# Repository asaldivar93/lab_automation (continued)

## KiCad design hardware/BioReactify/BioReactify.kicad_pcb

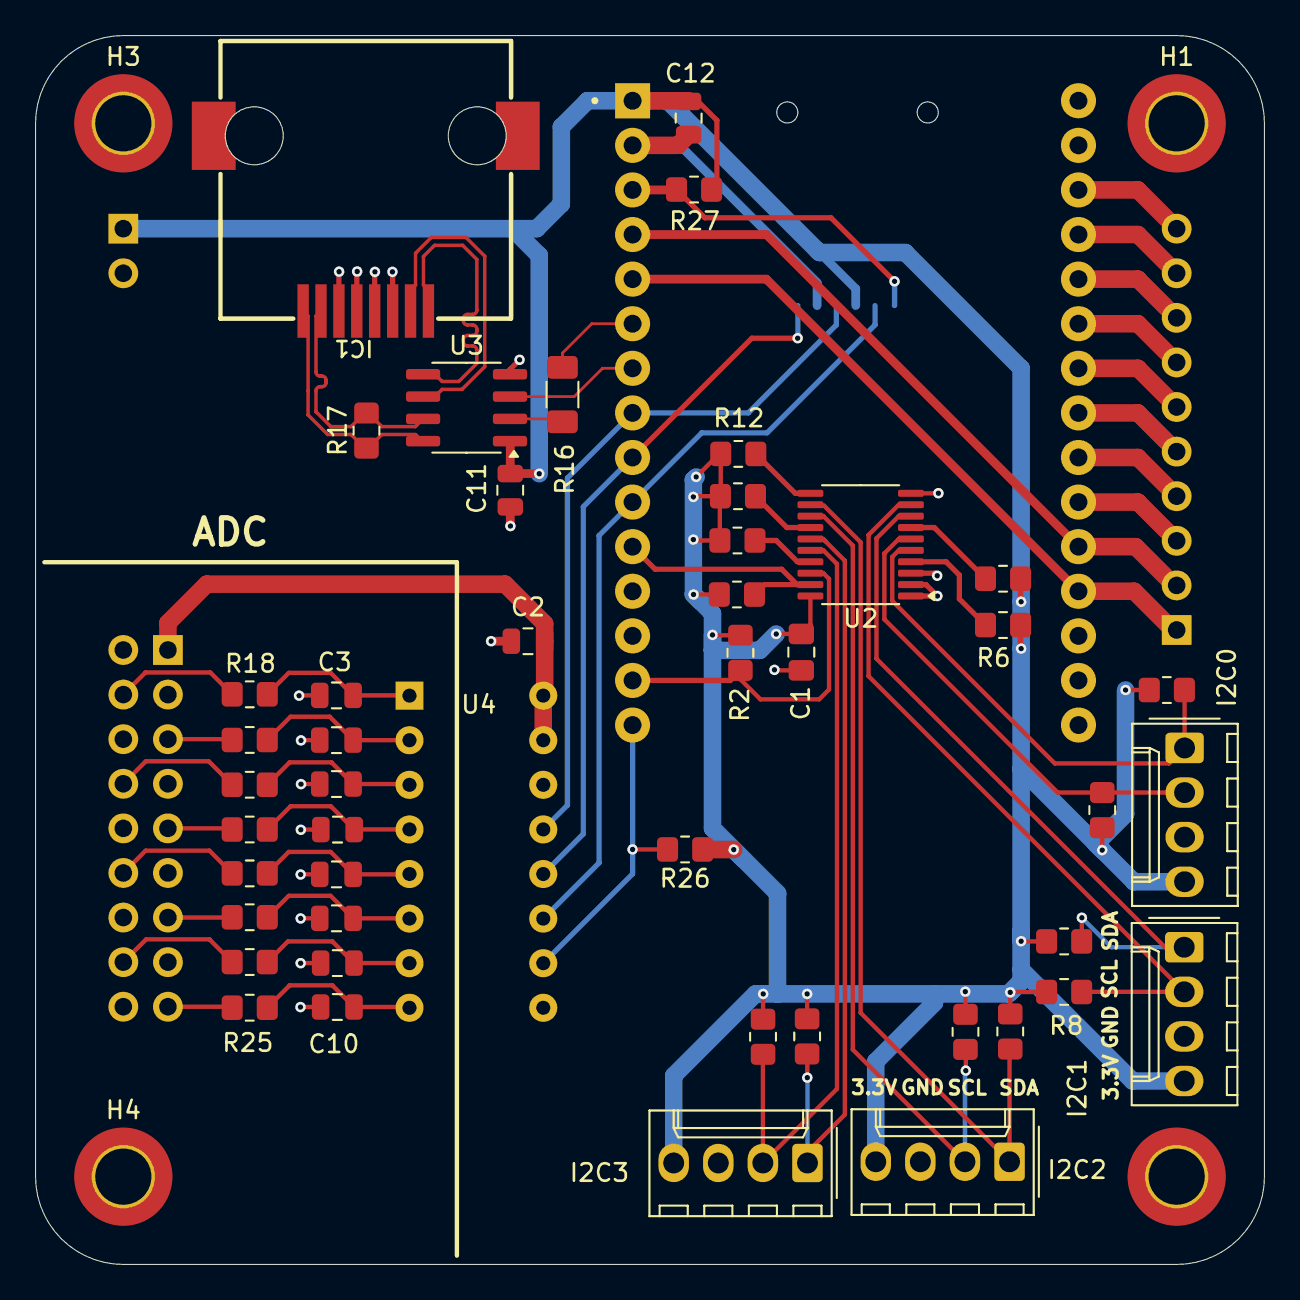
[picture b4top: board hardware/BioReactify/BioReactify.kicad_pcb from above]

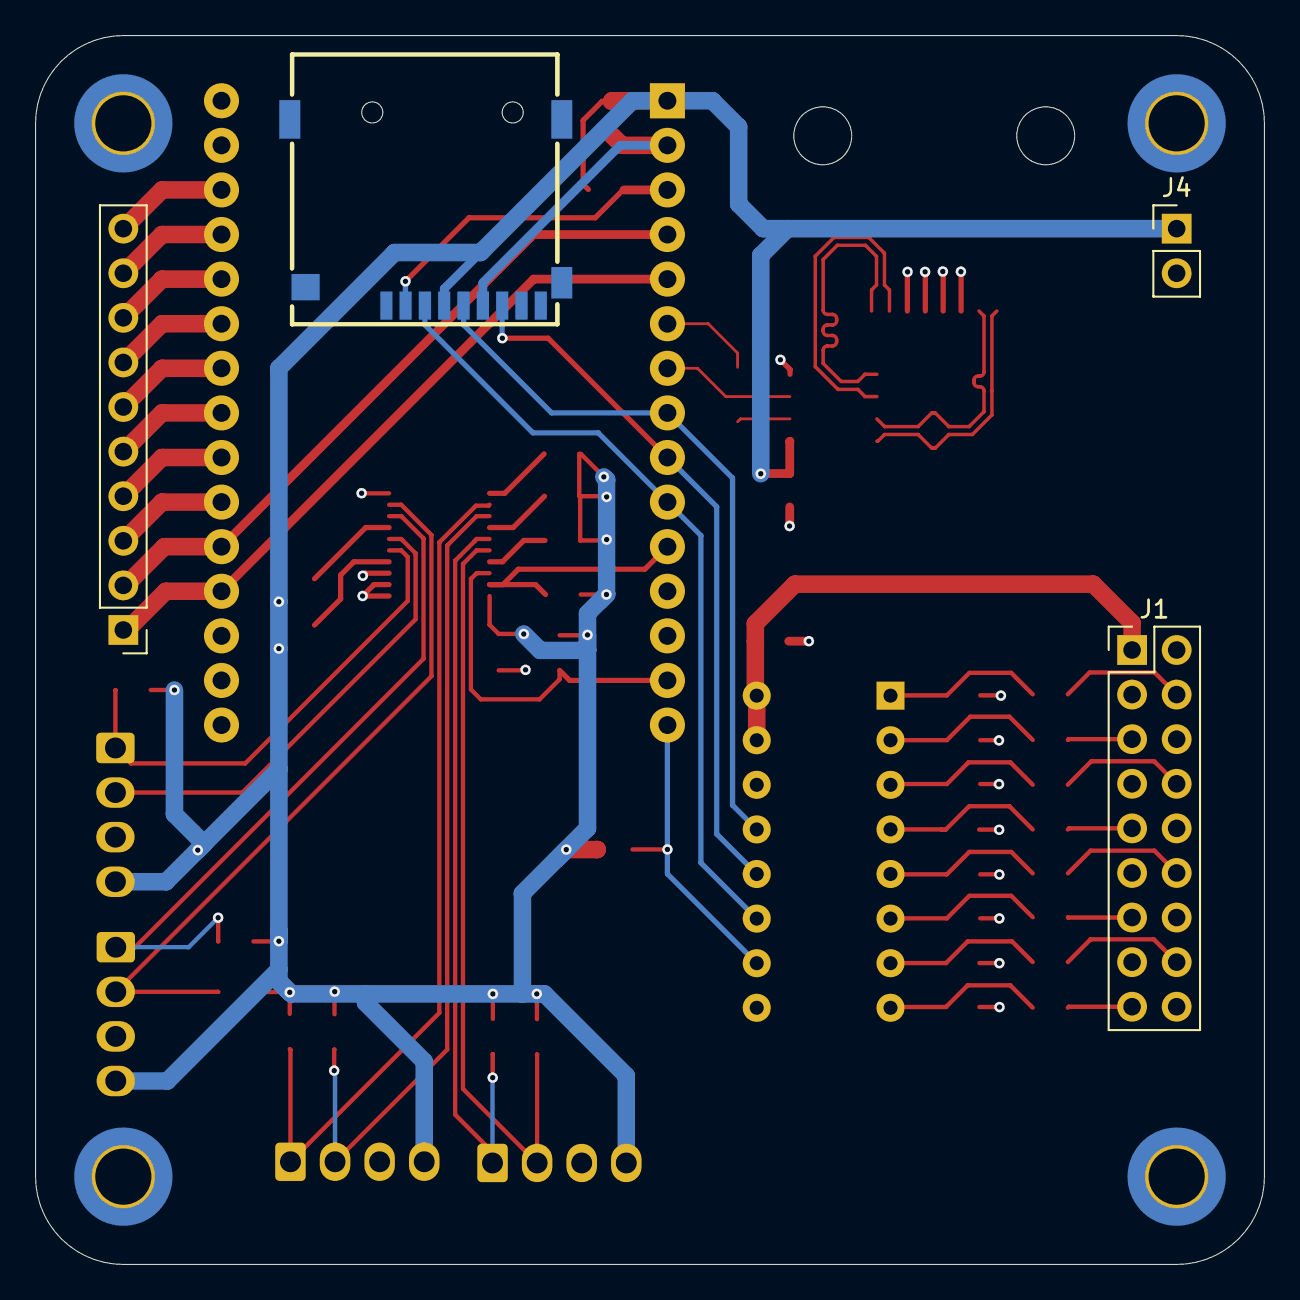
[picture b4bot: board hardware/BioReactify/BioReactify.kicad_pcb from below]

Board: 4 copper layers, 70.0 x 70.0 mm, 56 parts (4 on the bottom side), 56 nets.

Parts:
C1: 10uF; C_0805_2012Metric_Pad1.18x1.45mm_HandSolder
C2, C11, C12: 10uF; C_0805_2012Metric
C3, C4, C5, C6, C7, C8, C9, C10: 0.022uF; C_0805_2012Metric
H1, H2, H3, H4: MountingHole_Pad; MountingHole_3.2mm_M3_DIN965_Pad_TopBottom
I2C0, I2C1, I2C2, I2C3: Conn_01x04_Pin; Molex_KK-254_AE-6410-04A_1x04_P2.54mm_Vertical
IC1: MJ5688-B111-HR1-C; RJ45-TH_MJ5688-B111-HR1-C
J1: Conn_02x09_Odd_Even; PinHeader_2x09_P2.54mm_Vertical
J2: Conn_01x10_Pin; PinHeader_1x10_P2.54mm_Vertical
J3: Micro_SD_Card; TF-SMD_THD2528-11SD-GF
J4: Conn_01x02_Pin; PinHeader_1x02_P2.54mm_Vertical
R1, R2, R3, R4, R5, R6, R7, R8, R9, R10, R11, R12, R13, R14, R15, R26, R27: 10K; R_0805_2012Metric_Pad1.20x1.40mm_HandSolder
R16: 0; R_1206_3216Metric_Pad1.30x1.75mm_HandSolder
R17, R18, R19, R20, R21, R22, R23, R24, R25: 100; R_0805_2012Metric_Pad1.20x1.40mm_HandSolder
U1: ESP32-DEVKIT-V1; MODULE_ESP32_DEVKIT_V1
U2: TCA9544A; TSSOP-20_4.4x6.5mm_P0.65mm
U3: MAX3490xSA; SOIC-8_3.9x4.9mm_P1.27mm
U4: MCP3208; DIP-16_W7.62mm_Socket

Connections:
+3.3VADC: C2.1, J1.1, U4.15 (Vref), U4.16 (Vdd)
/ADC/CH0: C3.1, R18.1, U4.1 (CH0)
/ADC/CH1: C4.1, R19.1, U4.2 (CH1)
/ADC/CH2: C5.1, R20.1, U4.3 (CH2)
/ADC/CH3: C6.1, R21.1, U4.4 (CH3)
/ADC/CH4: C7.1, R22.1, U4.5 (CH4)
/ADC/CH5: C8.1, R23.1, U4.6 (CH5)
/ADC/CH6: C9.1, R24.1, U4.7 (CH6)
/ADC/CH7: C10.1, R25.1, U4.8 (CH7)
/ADC/INCH0: J1.4, R18.2
/ADC/INCH1: J1.5, R19.2
/ADC/INCH2: J1.8, R20.2
/ADC/INCH3: J1.9, R21.2
/ADC/INCH4: J1.12, R22.2
/ADC/INCH5: J1.13, R23.2
/ADC/INCH6: J1.16, R24.2
/ADC/INCH7: J1.17, R25.2
/CS: R26.2, U1.15 (D23), U4.10 (~CS/SHDN)
/CS1: J3.2 (DAT3/CD), R27.2, U1.3 (D15)
/D2: J2.2, U1.4 (D2), U1.20 (D35)
/D4: J2.1, U1.5 (D4), U1.19 (D34)
/DAC1: J2.5, U1.23 (D25)
/DAC2: J2.6, U1.24 (D26)
/I2C/INT0: R6.2, U2.4 (~INT0)
/I2C/INT1: R9.2, U2.7 (~INT1)
/I2C/INT2: R12.2, U2.11 (~INT2)
/I2C/INT3: R15.2, U2.14 (~INT3)
/I2C/SC0: I2C0.2, R5.2, U2.6 (SC0)
/I2C/SC1: I2C1.2, R8.2, U2.9 (SC1)
/I2C/SC2: I2C2.2, R11.2, U2.13 (SC2)
/I2C/SC3: I2C3.2, R14.2, U2.16 (SC3)
/I2C/SD0: I2C0.1, R4.2, U2.5 (SD0)
/I2C/SD1: I2C1.1, R7.2, U2.8 (SD1)
/I2C/SD2: I2C2.1, R10.2, U2.12 (SD2)
/I2C/SD3: I2C3.1, R13.2, U2.15 (SD3)
/MISO: J3.7 (DAT0), U1.9 (D18), U4.12 (Dout)
/MOSI: J3.3 (CMD), U1.10 (D19), U4.11 (Din)
/RS485/R0: R16.2, U3.2 (RO)
/RS485/RX2: R16.1, U1.6 (RX2)
/RS485/RX_N: IC1.2, R17.2, U3.7 (B)
/RS485/RX_P: IC1.1, R17.1, U3.8 (A)
/RS485/TX2: U1.7 (TX2), U3.3 (DI)
/RS485/TX_N: IC1.7, U3.6 (Z)
/RS485/TX_P: IC1.8, U3.5 (Y)
/SCL: R2.2, U1.14 (D22), U2.18 (SCL)
/SCLK: J3.5 (CLK), U1.8 (D5), U4.13 (CLK)
/SDA: R1.2, U1.11 (D21), U2.19 (SDA)
GND: C1.2, C2.2, C3.2, C4.2, C5.2, C6.2, C7.2, C8.2, C9.2, C10.2, C11.2, C12.2, H1.1, H2.1, H3.1, H4.1, I2C0.3, I2C1.3, I2C2.3, I2C3.3, IC1.3, IC1.4, IC1.5, IC1.6, J1.2, J1.3, J1.6, J1.7, J1.10, J1.11, J1.14, J1.15, J1.18, J3.6 (VSS), J4.2, U1.2 (GND), U1.29 (GND), U2.1 (A0), U2.2 (A1), U2.3 (A2), U2.10 (GND), U3.4 (GND), U4.9 (DGND), U4.14 (AGND)
unnamed: J2.3, U1.21 (D32)
unnamed: J2.4, U1.22 (D33)
unnamed: J2.7, U1.25 (D27)
unnamed: J2.8, U1.26 (D14)
unnamed: J2.9, U1.27 (D12)
unnamed: J2.10, U1.28 (D13)
unnamed: R3.2, U2.17 (~INT)
VDD: C1.1, C11.1, C12.1, I2C0.4, I2C1.4, I2C2.4, I2C3.4, J3.4 (VDD), J4.1, R1.1, R2.1, R3.1, R4.1, R5.1, R6.1, R7.1, R8.1, R9.1, R10.1, R11.1, R12.1, R13.1, R14.1, R15.1, R26.1, R27.1, U1.1 (3V3), U2.20 (VCC), U3.1 (VCC)

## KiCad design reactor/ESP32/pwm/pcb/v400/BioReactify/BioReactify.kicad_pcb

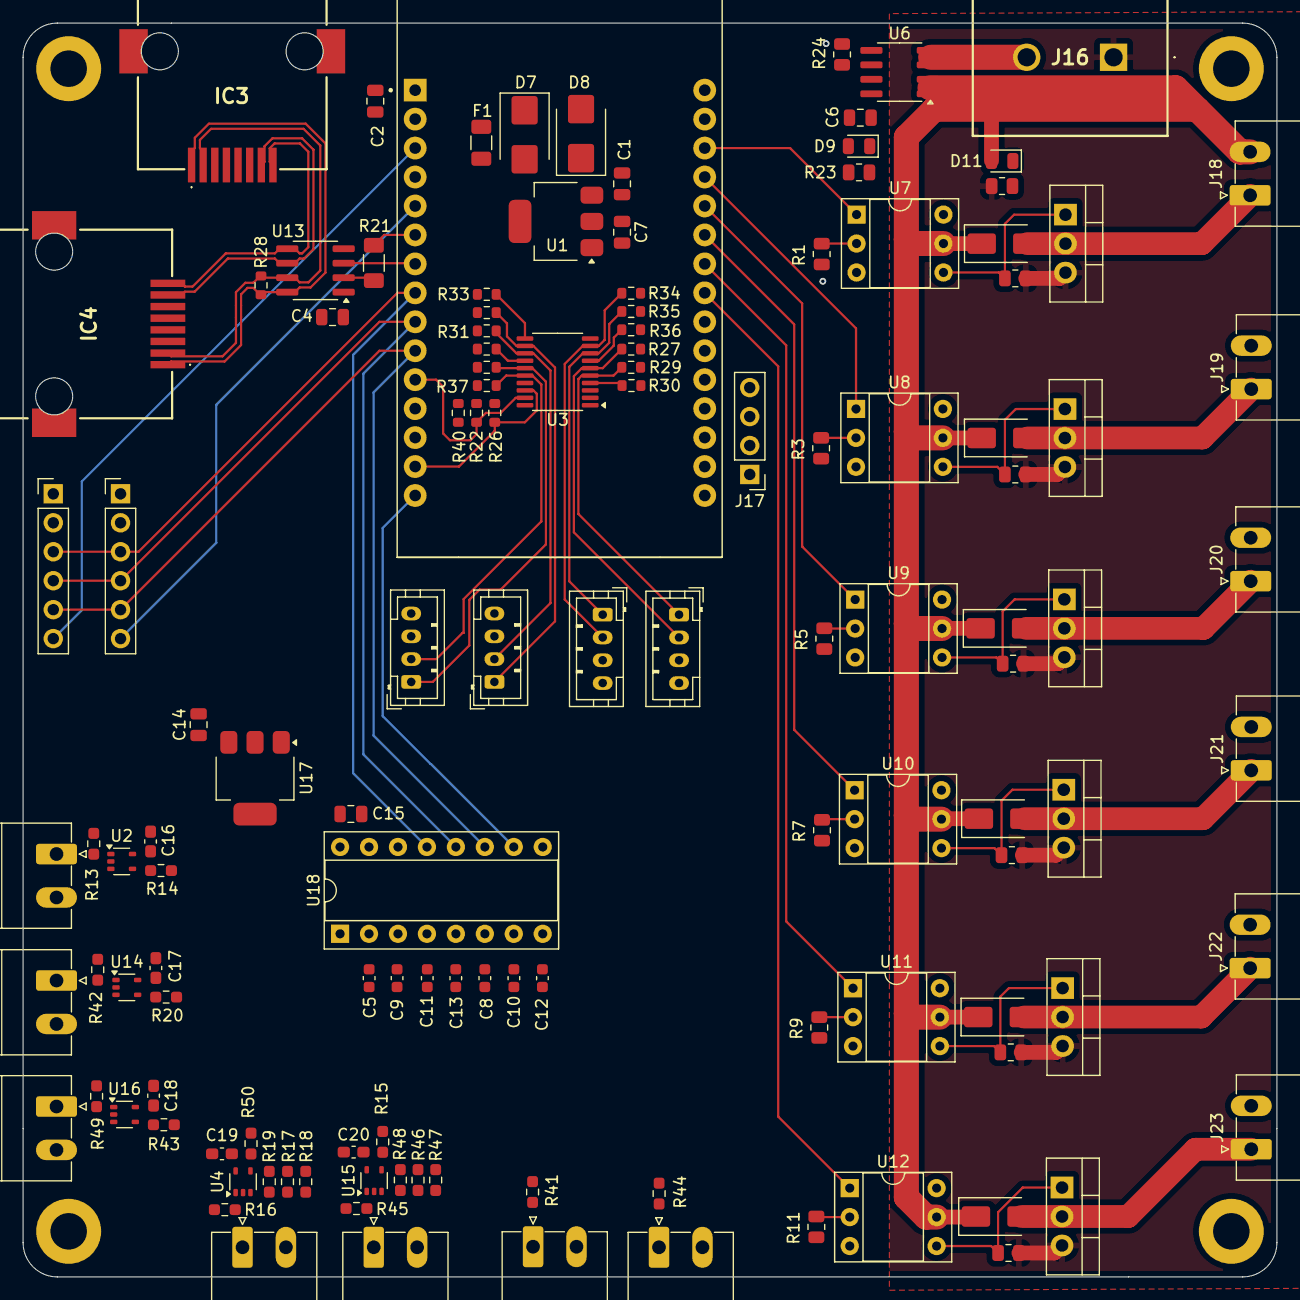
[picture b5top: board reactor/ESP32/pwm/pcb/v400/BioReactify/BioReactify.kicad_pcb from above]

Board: 4 copper layers, 110.0 x 110.0 mm, 131 parts (0 on the bottom side), 89 nets.

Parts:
C1, C14: 100nF; C_0805_2012Metric
C2, C4, C6, C7, C15: 10uF; C_0805_2012Metric
C5, C8, C9, C10, C11, C12, C13: 0.047uf; C_0603_1608Metric
C16, C17, C18, C19, C20: 0.1uF; C_0603_1608Metric_Pad1.08x0.95mm_HandSolder
D1, D2, D3, D4, D5, D6: 50V 5A; D_SMA
D7: 50V 2A; D_SMB
D8: 5.1V; D_SMB
D9, D11: LED; LED_0805_2012Metric
F1: 6V 1.5A; Fuse_1206_3216Metric
H1, H2, H3, H4: MountingHole_Pad; MountingHole_3.2mm_M3_ISO7380_Pad
IC3, IC4: MJ5688-B111-HR1-C; MJ5688B111HR1C
J1, J2, J3, J4, J5, J6, J7, J18, J19, J20, J21, J22, J23: Conn_01x02; PhoenixContact_MC_1,5_2-G-3.81_1x02_P3.81mm_Horizontal
J9, J10: Conn_01x06_Pin; PinHeader_1x06_P2.54mm_Vertical
J11, J12, J13, J14: Conn_01x04_Pin; JST_PH_B4B-PH-K_1x04_P2.00mm_Vertical
J16: KF25C-7.62-2P; KF25C7622P
J17: Conn_01x04_Pin; PinHeader_1x04_P2.54mm_Vertical
Q1, Q2, Q3, Q4, Q5, Q6: IRLZ44N; TO-220-3_Vertical
R1, R3, R5, R7, R9, R11, R23: 100; R_0805_2012Metric
R2, R4, R6, R8, R10, R12: 470; R_0805_2012Metric
R13, R42, R49: 150; R_0603_1608Metric_Pad0.98x0.95mm_HandSolder
R14, R15, R20, R41, R43, R44, R50: 3.4K; R_0603_1608Metric_Pad0.98x0.95mm_HandSolder
R16, R45: 7.8K; R_0603_1608Metric_Pad0.98x0.95mm_HandSolder
R17, R18, R46, R47: 4.1K; R_0603_1608Metric_Pad0.98x0.95mm_HandSolder
R19, R48: 1.5K; R_0603_1608Metric_Pad0.98x0.95mm_HandSolder
R21: 0; R_1206_3216Metric_Pad1.30x1.75mm_HandSolder
R22, R26, R27, R29, R30, R31, R32, R33, R34, R35, R36, R37, R38, R39, R40: 10K; R_0603_1608Metric
R24: 10K; R_0805_2012Metric
R25: 550; R_0805_2012Metric
R28: 120; R_0603_1608Metric
U1, U17: LD1117S33TR_SOT223; SOT-223-3_TabPin2
U2, U4, U14, U15, U16: TLV9001IDCK; SOT-353_SC-70-5
U3: TCA9544A; TSSOP-20_4.4x6.5mm_P0.65mm
U5: ESP32-DEVKIT-V1; MODULE_ESP32_DEVKIT_V1
U6: ACS712xLCBTR-030B3; SOIC-8_3.9x4.9mm_P1.27mm
U7, U8, U9, U10, U11, U12: 4N25; DIP-6_W7.62mm_Socket
U13: MAX3490xSA; SOIC-8_3.9x4.9mm_P1.27mm
U18: MCP3208; DIP-16_W7.62mm_Socket

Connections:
+3.3V: C2.1, C4.1, C6.1, C7.1, D9.2 (A), J9.1, J10.1, J11.4, J12.4, J13.4, J14.4, R22.1, R24.1, R26.1, R27.1, R29.1, R30.1, R31.1, R32.1, R33.1, R34.1, R35.1, R36.1, R37.1, R38.1, R39.1, R40.1, U1.2 (VO), U3.20 (VCC), U5.1 (3V3), U6.8 (VCC), U13.1 (VCC)
+3.3VADC: C15.1, C16.1, C17.1, C18.1, C19.1, C20.1, J4.1, J5.1, R17.2, R46.2, U2.5 (V+), U4.5 (V+), U14.5 (V+), U15.5 (V+), U16.5 (V+), U17.2 (VO), U18.15 (Vref), U18.16 (Vdd)
+12V: D1.1 (K), D2.1 (K), D3.1 (K), D4.1 (K), D5.1 (K), D6.1 (K), D11.2 (A), J18.2, J19.2, J20.2, J21.2, J22.2, J23.2, U6.1 (IP+), U6.2 (IP+), U7.5, U8.5, U9.5, U10.5, U11.5, U12.5
-12V: J16.1, Q1.3 (S), Q2.3 (S), Q3.3 (S), Q4.3 (S), Q5.3 (S), Q6.3 (S), R2.2, R4.2, R6.2, R8.2, R10.2, R12.2, R25.1
/5v_protected: C1.1, C14.1, D7.1 (K), D8.1 (K), U1.3 (VI), U17.3 (VI)
/12v_in: J16.2, U6.3 (IP-), U6.4 (IP-)
/CH0: U6.7 (VIOUT), U18.1 (CH0)
/CS0: U5.15 (D23), U18.10 (~CS/SHDN)
/CS2: J9.6, U5.5 (D4)
/CS3: J10.6, U5.3 (D15)
/D32: J17.3, U5.21 (D32)
/D33: J17.4, U5.22 (D33)
/D34: J17.2, U5.20 (D35)
/D35: J17.1, U5.19 (D34)
/FETNEG0: D1.2 (A), J18.1, Q1.2 (D)
/FETNEG1: D2.2 (A), J19.1, Q2.2 (D)
/FETNEG2: D3.2 (A), J20.1, Q3.2 (D)
/FETNEG3: D4.2 (A), J21.1, Q4.2 (D)
/FETNEG4: D5.2 (A), J22.1, Q5.2 (D)
/FETNEG5: D6.2 (A), J23.1, Q6.2 (D)
/PQ0: Q1.1 (G), R2.1, U7.4
/PQ1: Q2.1 (G), R4.1, U8.4
/PQ2: Q3.1 (G), R6.1, U9.4
/PQ3: Q4.1 (G), R8.1, U10.4
/PQ4: Q5.1 (G), R10.1, U11.4
/PQ5: Q6.1 (G), R12.1, U12.4
/Q0: U5.28 (D13), U7.1
/Q1: U5.27 (D12), U8.1
/Q2: U5.26 (D14), U9.1
/Q3: U5.25 (D27), U10.1
/Q4: U5.24 (D26), U11.1
/Q5: U5.23 (D25), U12.1
/R0: R21.2, U13.2 (RO)
/RX2: R21.1, U5.6 (RX2)
/RX_N: IC3.2, IC4.2, R28.2, U13.7 (B)
/RX_P: IC3.1, IC4.1, R28.1, U13.8 (A)
/SCL: R26.2, U3.18 (SCL), U5.14 (D22)
/SDA: R22.2, U3.19 (SDA), U5.11 (D21)
/SPI_CLK: J9.3, J10.3, U5.8 (D5), U18.13 (CLK)
/SPI_DIN: J9.5, J10.5, U5.10 (D19), U18.11 (Din)
/SPI_DOUT: J9.4, J10.4, U5.9 (D18), U18.12 (Dout)
/SQ0: R1.1, U7.2
/SQ1: R3.1, U8.2
/SQ2: R5.1, U9.2
/SQ3: R7.1, U10.2
/SQ4: R9.1, U11.2
/SQ5: R11.1, U12.2
/TX2: U5.7 (TX2), U13.3 (DI)
/TX_N: IC3.7, IC4.7, U13.6 (Z)
/TX_P: IC3.8, IC4.8, U13.5 (Y)
/adc0/CH1: C5.1, R14.1, U18.2 (CH1)
/adc0/CH2: C9.1, R20.1, U18.3 (CH2)
/adc0/CH3: C11.1, R43.1, U18.4 (CH3)
/adc0/CH4: C13.1, R50.1, U18.5 (CH4)
/adc0/CH5: C8.1, R15.1, U18.6 (CH5)
/adc0/CH6: C10.1, R41.1, U18.7 (CH6)
/adc0/CH7: C12.1, R44.1, U18.8 (CH7)
/adc0/ICH1: R14.2, U2.3 (-), U2.4
/adc0/ICH2: R20.2, U14.3 (-), U14.4
/adc0/ICH3: R43.2, U16.3 (-), U16.4
/adc0/IN1: J1.1, R13.2, U2.1 (+)
/adc0/IN2: J2.1, R42.2, U14.1 (+)
/adc0/IN3: J3.1, R49.2, U16.1 (+)
/adc0/IN4: J4.2, R16.2, U4.1 (+)
/adc0/IN5: J5.2, R45.2, U15.1 (+)
/adc0/IN6: J6.1, R41.2
/adc0/IN7: J7.1, R44.2
/adc0/TCH4: R19.2, R50.2, U4.4
/adc0/TCH5: R15.2, R48.2, U15.4
/fuse_5v: D7.2 (A), F1.2
/i2c/INT0: R30.2, U3.4 (~INT0)
/i2c/INT1: R36.2, U3.7 (~INT1)
/i2c/INT2: R33.2, U3.11 (~INT2)
/i2c/INT3: R39.2, U3.14 (~INT3)
/i2c/SC0: J11.2, R27.2, U3.6 (SC0)
/i2c/SC1: J12.2, R34.2, U3.9 (SC1)
/i2c/SC2: J13.2, R31.2, U3.13 (SC2)
/i2c/SC3: J14.2, R37.2, U3.16 (SC3)
/i2c/SD0: J11.1, R29.2, U3.5 (SD0)
/i2c/SD1: J12.1, R35.2, U3.8 (SD1)
/i2c/SD2: J13.1, R32.2, U3.12 (SD2)
/i2c/SD3: J14.1, R38.2, U3.15 (SD3)
/led_3v3: D9.1 (K), R23.2
/led_12v: D11.1 (K), R25.2
GND: C1.2, C2.2, C4.2, C5.2, C6.2, C7.2, C8.2, C9.2, C10.2, C11.2, C12.2, C13.2, C14.2, C15.2, C16.2, C17.2, C18.2, C19.2, C20.2, D8.2 (A), IC3.3, IC3.4, IC3.5, IC3.6, IC4.3, IC4.4, IC4.5, IC4.6, J1.2, J2.2, J3.2, J6.2, J7.2, J9.2, J10.2, J11.3, J12.3, J13.3, J14.3, R1.2, R3.2, R5.2, R7.2, R9.2, R11.2, R13.1, R16.1, R18.1, R23.1, R42.1, R45.1, R47.1, R49.1, U1.1 (GND), U2.2 (V-), U3.1 (A0), U3.2 (A1), U3.3 (A2), U3.10 (GND), U4.2 (V-), U5.2 (GND), U5.29 (GND), U6.5 (GND), U13.4 (GND), U14.2 (V-), U15.2 (V-), U16.2 (V-), U17.1 (GND), U18.9 (DGND), U18.14 (AGND)
unnamed: R40.2, U3.17 (~INT)
unnamed: R17.1, R18.2, R19.1, U4.3 (-)
unnamed: R24.2, U6.6 (FAULT)
unnamed: R46.1, R47.2, R48.1, U15.3 (-)

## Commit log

2023-10-28 Serial comms fixed
2023-11-06 incomplete MHE
2023-11-07 complete mhe stirrer
2023-11-09 Methods for reactor temperature PID calibration
2023-11-11 Fixed MHE for reactor electric heater
2023-11-15 Added reactor control files
2023-11-30 plots_tutorial
2024-01-16 updated heat balance model and pid
2024-01-18 Up to 8 ON/OFF timers in parallel
2024-01-22 low pass filter on T_reactor
2024-01-24 prototype flow meter
2024-03-03 board v302 prototype, classes board, exp, sqlite
2024-03-03 case PID, missing: initialize filter, turn pid on/off, link control_var
2024-03-04 completed toggle control in arduino, missing toggle control in python
2024-03-05 config_observer and update_config, missing: online_plot
2024-03-05 online_plotter, missing: slaves communication
2024-03-06 slaves comms config update prototype, missing: slaves info request
2024-03-06 setup logger, missing: slaves info request prototype
2024-03-08 minor bugs fixed, missing slaves info request
2024-03-09 minor bugs in parse command
2024-03-10 board.reconnect(), set save period, minor bugs
2024-03-24 slaves serial comms, update missing to python board_info and get_data
2024-03-25 class Sensors(i2c,spi),dualcore-serialcomms,missing:update python comms
2024-03-26 fixed bugs in slavecomms, request_board_info, missing: save_data
2024-03-26 save_data
2024-03-27 flow sensor, missing: flow sensor test, save_data
2024-04-01 missing: flow sensor/save_data test, serial send_data frequency eval
2024-04-02 fully tested: flowsensor, slavescoms(slaverequest:200ms), savedata :)
2024-04-02 license
2024-04-02 other
2024-04-08 espnow prototype
2024-05-16 Output class in cpp; Connect 2 boards to 1 experiment
2024-05-16 Added logger
2024-05-18 Fixed bug in PID computation. Adder Readme
2024-05-20 Added diff_press sensor (sen0343)
2024-05-26 update pcb: incomplete
2024-06-13 PCB complete, biomass sensor PCB complete
2024-06-26 Hardware updated
2024-07-04 created inputs class, added DAC channels
2024-07-08 new sensors; bug fix;
2024-07-16 ESP32 examples
2024-08-04 bug fix; reactor board update;
